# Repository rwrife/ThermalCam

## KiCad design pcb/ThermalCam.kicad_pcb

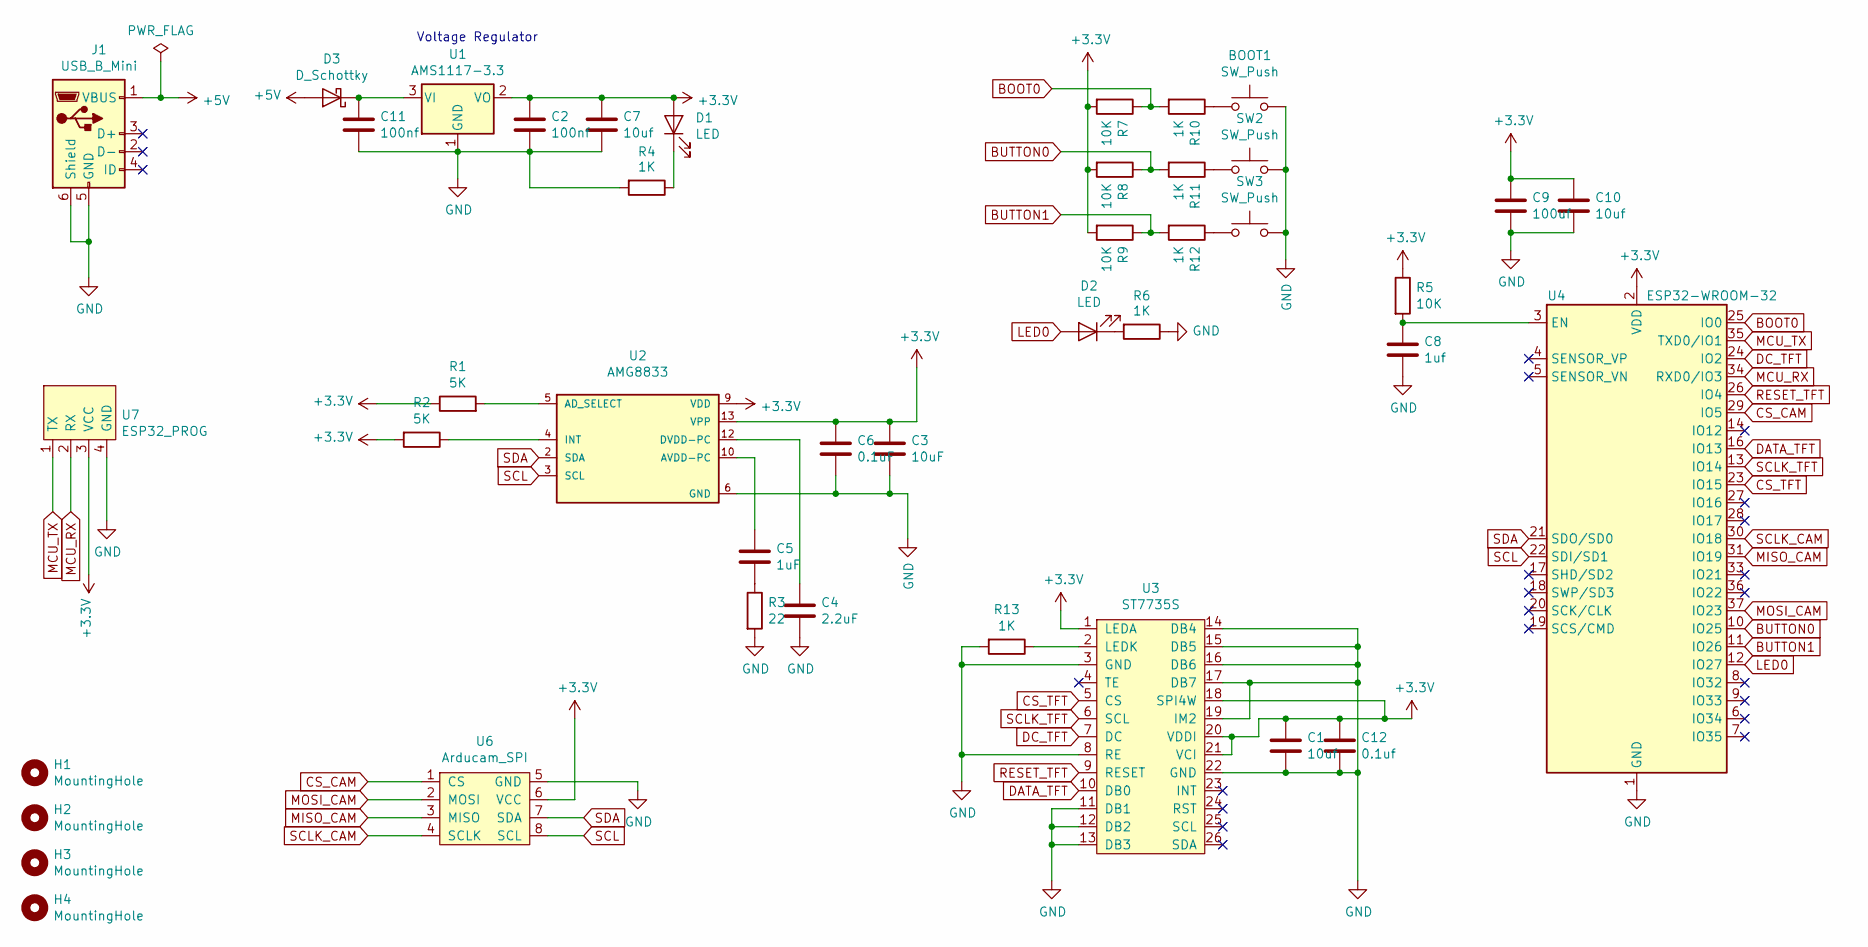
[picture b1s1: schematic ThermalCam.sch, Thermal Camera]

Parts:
BOOT1: SW_Push; SW_SPST_TL3342
C1, C7, C10: 10uf; C_1206_3216Metric
C2, C11: 100nf; C_1206_3216Metric
C3: 10uF; C_1206_3216Metric
C4: 2.2uF; C_1206_3216Metric
C5: 1uF; C_1206_3216Metric
C6: 0.1uF; C_1206_3216Metric
C8: 1uf; C_1206_3216Metric
C9: 100uf; C_1206_3216Metric
C12: 0.1uf; C_1206_3216Metric
D1, D2: LED; LED_1206_3216Metric
D3: D_Schottky; D_1206_3216Metric
H1, H2, H3, H4: MountingHole; MountingHole_2.2mm_M2
J1: USB_B_Mini; USB_Micro-B_Molex-105017-0001
R1, R2: 5K; R_1206_3216Metric
R3: 22; R_1206_3216Metric
R4, R6, R10, R11, R12, R13: 1K; R_1206_3216Metric
R5, R7, R8, R9: 10K; R_1206_3216Metric
SW2, SW3: SW_Push; SW_SPST_TL3342
U1: AMS1117-3.3; SOT-223-3_TabPin2
U2: AMG8833; XDCR_AMG8833
U3: ST7735S; ER-CON26HT-1
U4: ESP32-WROOM-32
U6: Arducam_SPI; PinHeader_1x08_P2.54mm_Vertical
U7: ESP32_PROG; PinHeader_1x04_P2.54mm_Vertical

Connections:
+3V3: C1.1, C2.1, C3.1, C6.1, C7.1, C9.1, C10.1, C12.1, D1.2 (A), R1.1, R2.2, R5.1, R7.2, R8.2, R9.2, U1.2 (VO), U2.9 (VDD), U2.13 (VPP), U3.1 (LEDA), U3.18 (SPI4W), U3.20 (VDDI), U3.21 (VCI), U4.2 (VDD), U6.6 (VCC), U7.3 (VCC)
+5V: D3.2 (A), J1.1 (VBUS)
BOOT0: R7.1, R10.2, U4.25 (IO0)
BUTTON0: R8.1, R11.2, U4.10 (IO25)
BUTTON1: R9.1, R12.2, U4.11 (IO26)
CS_CAM: U4.29 (IO5), U6.1 (CS)
CS_TFT: U3.5 (CS), U4.23 (IO15)
DATA_TFT: U3.10 (DB0), U4.16 (IO13)
DC_TFT: U3.7 (DC), U4.24 (IO2)
GND: BOOT1.2, C1.2, C2.2, C3.2, C4.2, C6.2, C7.2, C8.2, C9.2, C10.2, C11.2, C12.2, J1.5 (GND), J1.6 (Shield), R3.2, R4.2, R6.1, R13.2, SW2.2, SW3.2, U1.1 (GND), U2.6 (GND), U3.3 (GND), U3.8 (RE), U3.11 (DB1), U3.12 (DB2), U3.13 (DB3), U3.14 (DB4), U3.15 (DB5), U3.16 (DB6), U3.17 (DB7), U3.19 (IM2), U3.22 (GND), U4.1 (GND), U4.15 (GND), U4.38 (GND), U4.39 (GND), U6.5 (GND), U7.4 (GND)
LED0: D2.2 (A), U4.12 (IO27)
MCU_RX: U4.34 (RXD0/IO3), U7.2 (RX)
MCU_TX: U4.35 (TXD0/IO1), U7.1 (TX)
MISO_CAM: U4.31 (IO19), U6.3 (MISO)
MOSI_CAM: U4.37 (IO23), U6.2 (MOSI)
unnamed: BOOT1.1, R10.1
unnamed: C4.1, U2.12 (DVDD-PC)
unnamed: C5.1, U2.10 (AVDD-PC)
unnamed: C5.2, R3.1
unnamed: C8.1, R5.2, U4.3 (EN)
unnamed: C11.1, D3.1 (K), U1.3 (VI)
unnamed: D1.1 (K), R4.1
unnamed: D2.1 (K), R6.2
unnamed: R1.2, U2.5 (AD_SELECT)
unnamed: R2.1, U2.4 (INT)
unnamed: R11.1, SW2.1
unnamed: R12.1, SW3.1
unnamed: R13.1, U3.2 (LEDK)
RESET_TFT: U3.9 (RESET), U4.26 (IO4)
SCL: U2.3 (SCL), U4.22 (SDI/SD1), U6.8 (SCL)
SCLK_CAM: U4.30 (IO18), U6.4 (SCLK)
SCLK_TFT: U3.6 (SCL), U4.13 (IO14)
SDA: U2.2 (SDA), U4.21 (SDO/SD0), U6.7 (SDA)

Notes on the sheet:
Voltage Regulator

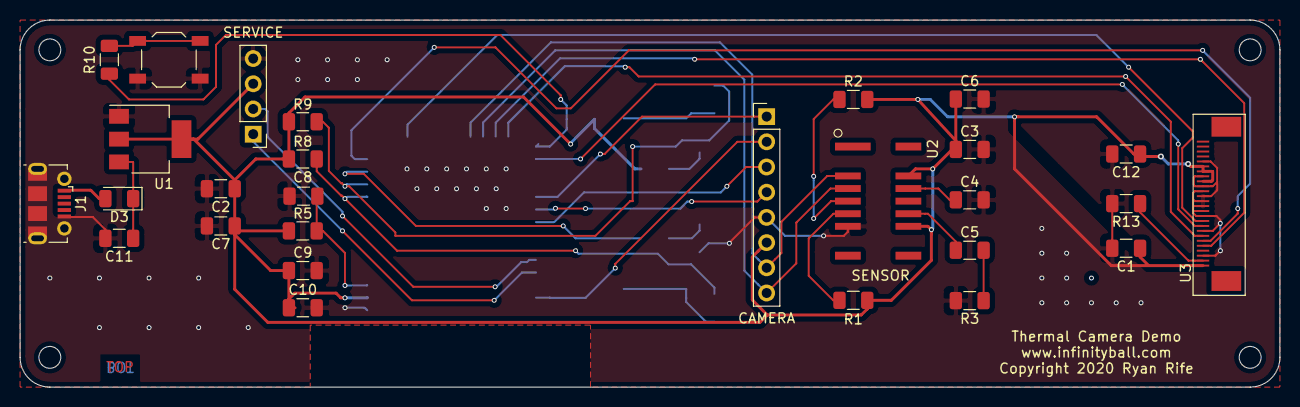
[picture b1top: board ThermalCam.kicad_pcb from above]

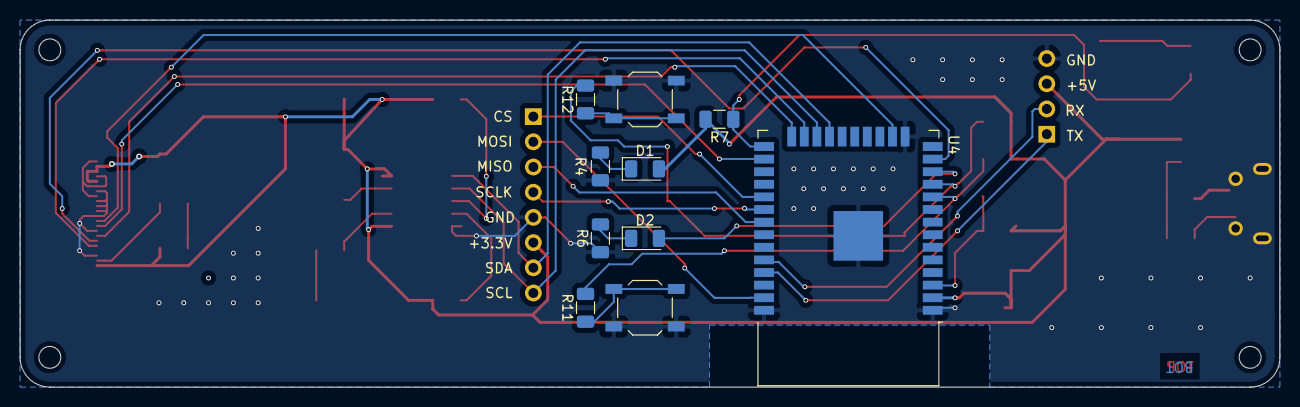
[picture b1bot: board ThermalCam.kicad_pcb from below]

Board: 2 copper layers, 127.0 x 37.0 mm, 42 parts (10 on the bottom side), 33 nets.

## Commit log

2020-05-04 Initial PCB.
2020-05-07 full rat nest connected
2020-05-23 added eastrising 1.44 tft

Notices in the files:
pcb/ThermalCam.kicad_pcb:
Copyright 2020 Ryan Rife
